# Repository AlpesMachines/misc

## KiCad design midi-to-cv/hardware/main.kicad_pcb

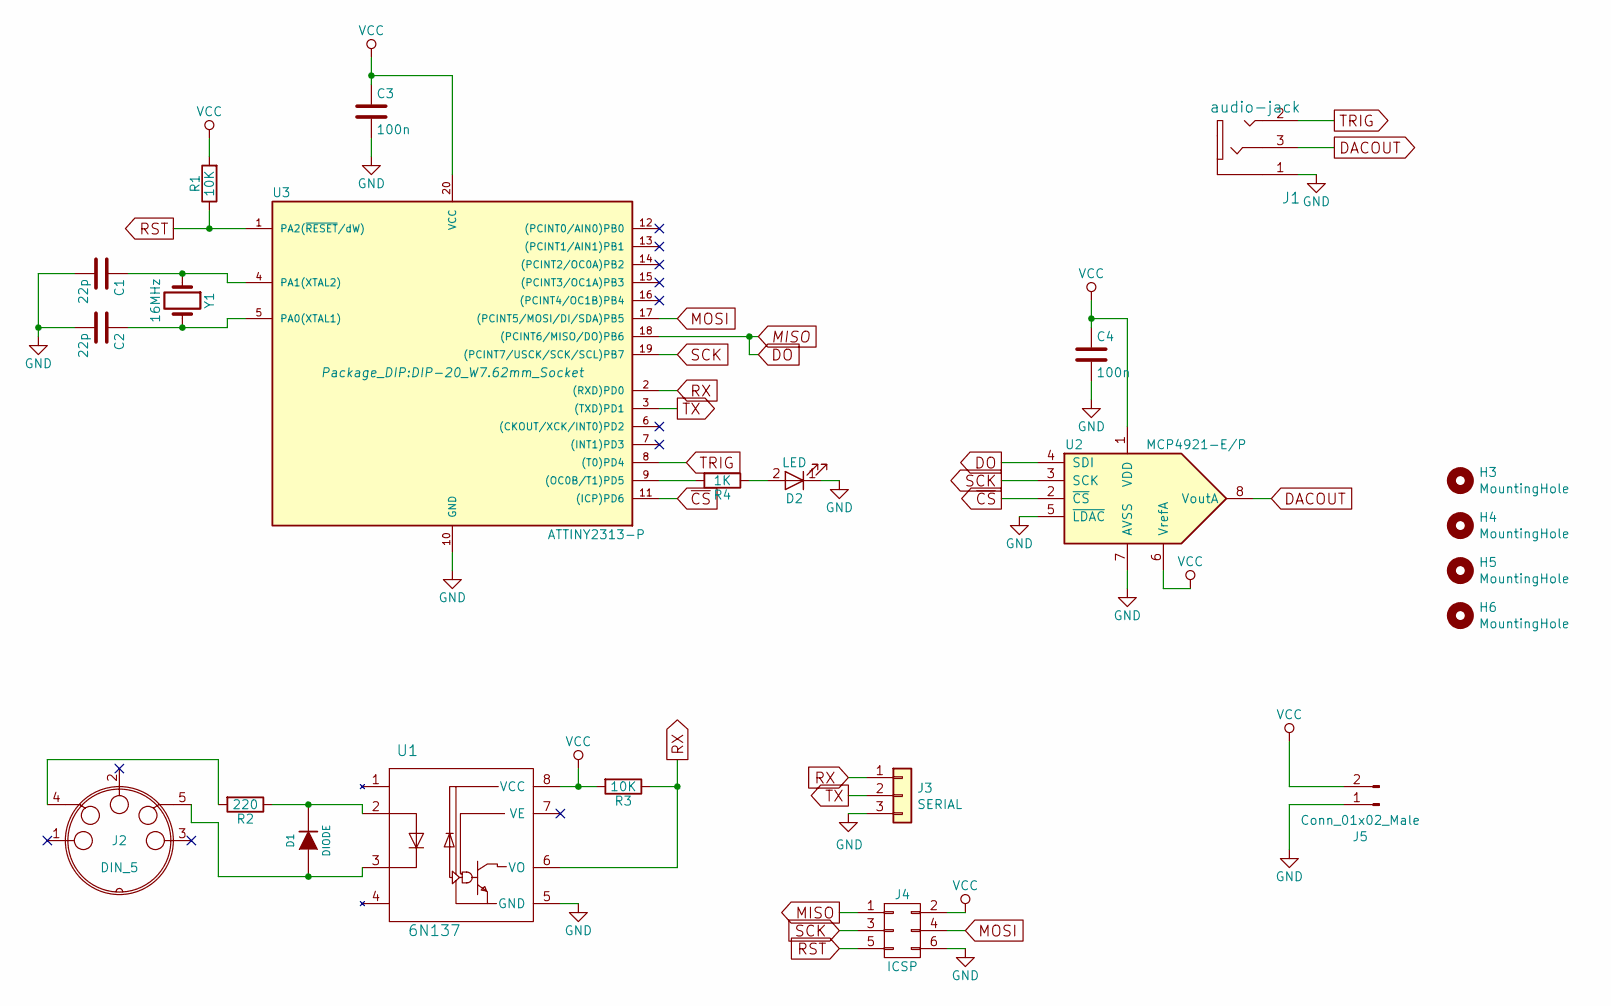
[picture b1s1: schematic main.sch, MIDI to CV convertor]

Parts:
C1, C2: 22p; C_Disc_D3.8mm_W2.6mm_P2.50mm
C3, C4: 100n; C_Disc_D4.3mm_W1.9mm_P5.00mm
D1: DIODE; D_T-1_P5.08mm_Horizontal
D2: LED; LED_D5.0mm
H3, H4, H5, H6: MountingHole; MountingHole_3.2mm_M3
J1: audio-jack; PJ-321
J2: DIN_5; din-5
J3: SERIAL; PinHeader_1x03_P2.54mm_Vertical
J4: ICSP; PinHeader_2x03_P2.54mm_Vertical
J5: Conn_01x02_Male; SolderWirePad_1x02_P5.08mm_Drill1.5mm
R1, R3: 10K; R_Axial_DIN0207_L6.3mm_D2.5mm_P7.62mm_Horizontal
R2: 220; R_Axial_DIN0207_L6.3mm_D2.5mm_P7.62mm_Horizontal
R4: 1K; R_Axial_DIN0207_L6.3mm_D2.5mm_P7.62mm_Horizontal
U1: 6N137; DIP-8_W7.62mm_Socket
U2: MCP4921-E/P; DIP-8_W7.62mm_Socket
U3: ATTINY2313-P; DIP-20_W7.62mm_Socket
Y1: 16MHz; Crystal_HC18-U_Vertical

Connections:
DACOUT: J1.3, U2.8 (VoutA)
DO: J4.1, U2.4 (SDI), U3.18 ((PCINT6/MISO/DO)PB6)
GND: C1.2, C2.2, C3.2, C4.2, D2.1 (K), J1.1, J3.3, J4.6, J5.1, U1.5 (GND), U2.5 (~LDAC~), U2.7 (AVSS), U3.10 (GND)
MOSI: J4.4, U3.17 ((PCINT5/MOSI/DI/SDA)PB5)
unnamed: C1.1, U3.4 (PA1(XTAL2)), Y1.1
unnamed: C2.1, U3.5 (PA0(XTAL1)), Y1.2
unnamed: D1.1 (A), J2.5, U1.3
unnamed: D1.2 (K), R2.1, U1.2
unnamed: D2.2 (A), R4.1
unnamed: J2.4, R2.2
unnamed: R4.2, U3.9 ((OC0B/T1)PD5)
RST: J4.5, R1.1, U3.1 (PA2(~RESET~/dW))
RX: J3.1, R3.1, U1.6 (VO), U3.2 ((RXD)PD0)
SCK: J4.3, U2.3 (SCK), U3.19 ((PCINT7/USCK/SCK/SCL)PB7)
TRIG: J1.2, U3.8 ((T0)PD4)
TX: J3.2, U3.3 ((TXD)PD1)
VCC: C3.1, C4.1, J4.2, J5.2, R1.2, R3.2, U1.8 (VCC), U2.1 (VDD), U2.6 (VrefA), U3.20 (VCC)
~CS: U2.2 (~CS~), U3.11 ((ICP)PD6)

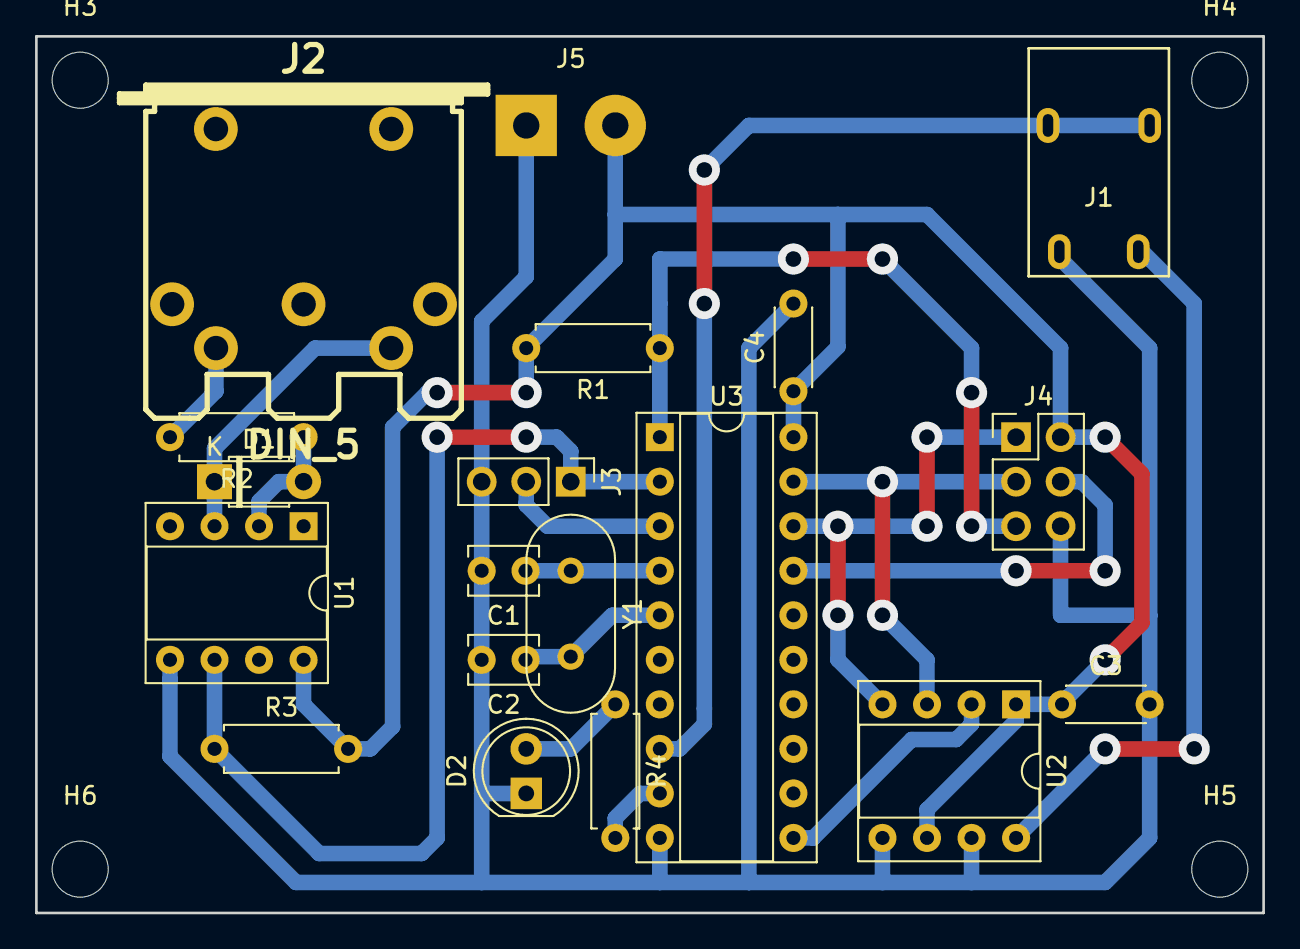
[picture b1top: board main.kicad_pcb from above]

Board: 2 copper layers, 70.0 x 50.0 mm, 23 parts (0 on the bottom side), 18 nets.

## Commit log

2019-02-20 Add midi-to-cv
2019-03-17 WIP: zebrak synth
2019-04-28 midi-to-cv: revision 3
